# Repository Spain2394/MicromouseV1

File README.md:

# Introduction
Micromouse (small robot car) PCB, boards are  designed in [EAGLE](http://eagle.autodesk.com)

Current board release [micromouse_board_revB_V0.0.16_2020-02-19.zip ](https://github.com/uga-robotics/MicromouseV1/blob/master/micromouse-main-board/micromouse-revB/micromouse_board_revB_V0.0.16_2020-02-19.zip ). Inside this zip file you will CAM files for assembly and manufacturing. 
Board BOM  --> [micromouse_board_revB_V0.0.16_2020-02-19.xlsx](https://github.com/uga-robotics/MicromouseV1/blob/master/micromouse-main-board/micromouse-revB/micromouse_board_revB_V0.0.16.xlsx)

## Getting going
Clone to hardware of software to local machine: ```git clone --recurse-submodules https://github.com/uga-robotics/MicromouseV1.git```

# Table of contents
1. [Bill Of Materials](https://github.com/Spain2394/MicromouseV1/blob/master/Wiki/Bill-of-Materials.md)
2. [Hardware Setup](https://github.com/Spain2394/MicromouseV1/blob/master/Wiki/Hardware-Setup.md)
3. [Software Setup](https://github.com/Spain2394/MicromouseV1/blob/master/Wiki/Software-Setup.md)

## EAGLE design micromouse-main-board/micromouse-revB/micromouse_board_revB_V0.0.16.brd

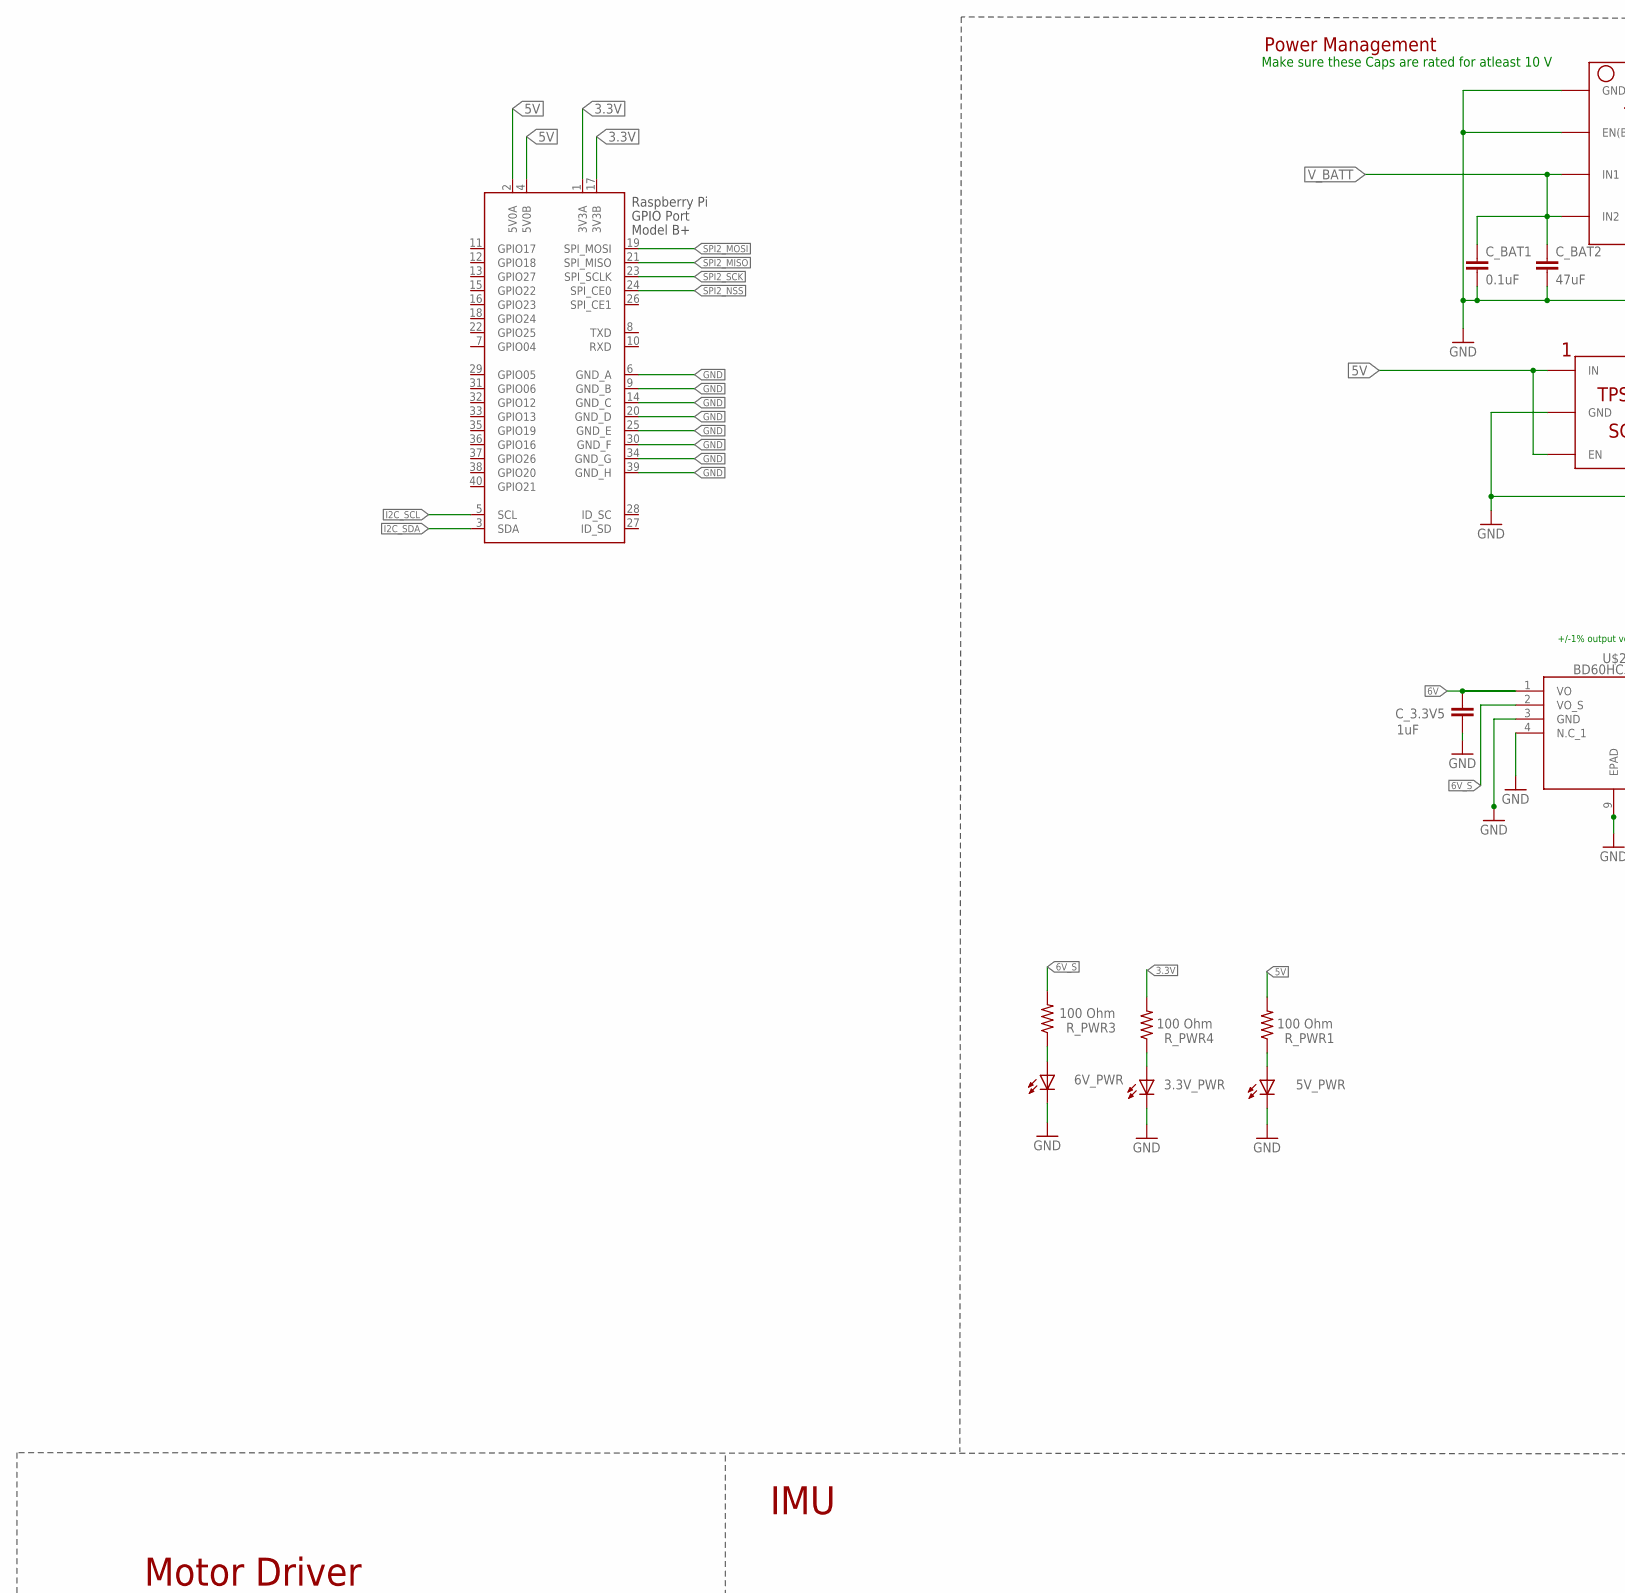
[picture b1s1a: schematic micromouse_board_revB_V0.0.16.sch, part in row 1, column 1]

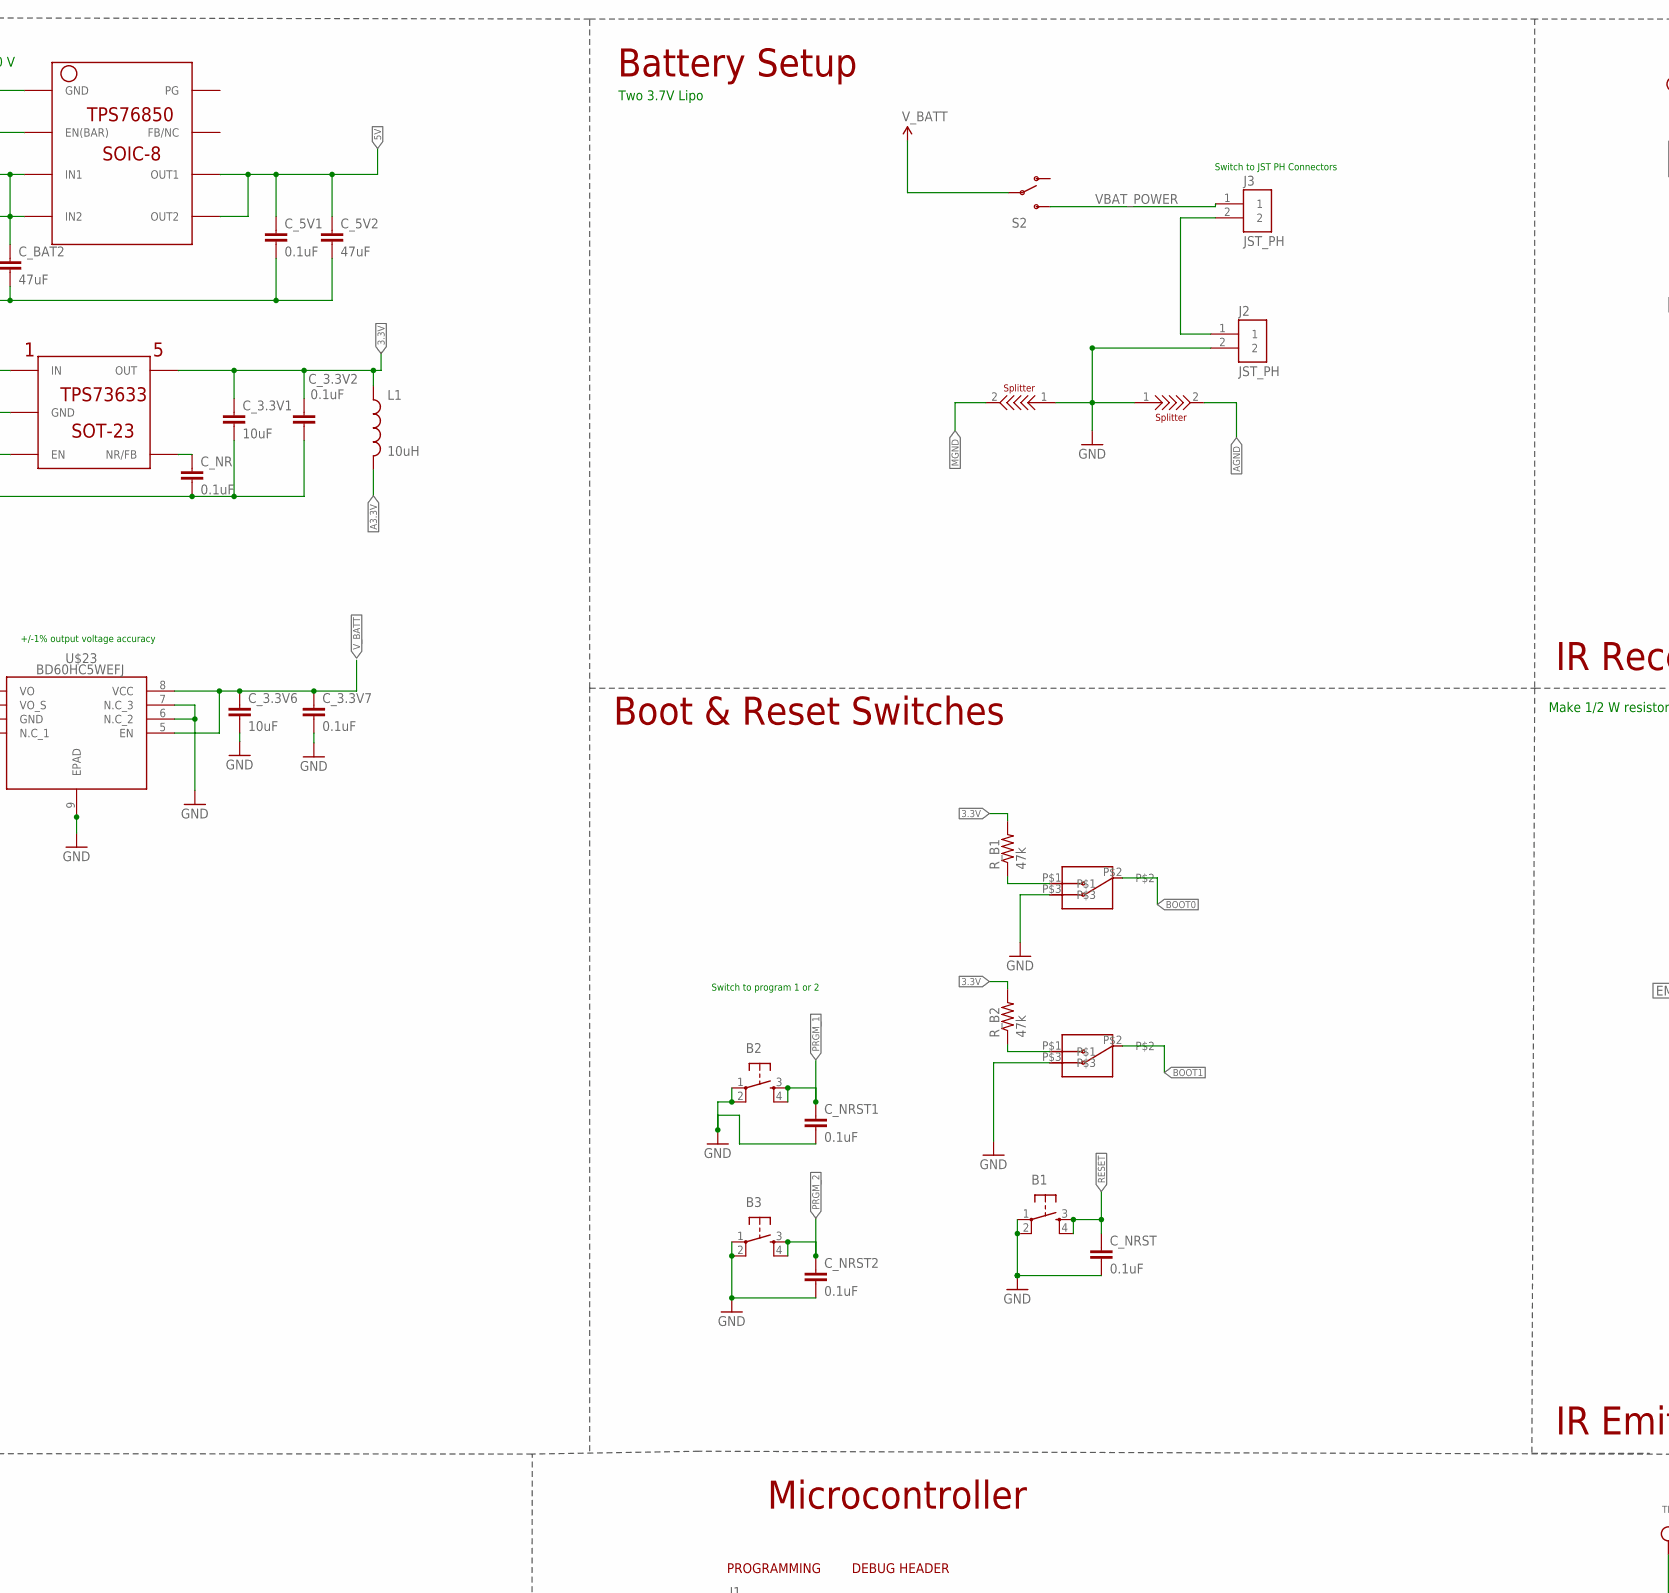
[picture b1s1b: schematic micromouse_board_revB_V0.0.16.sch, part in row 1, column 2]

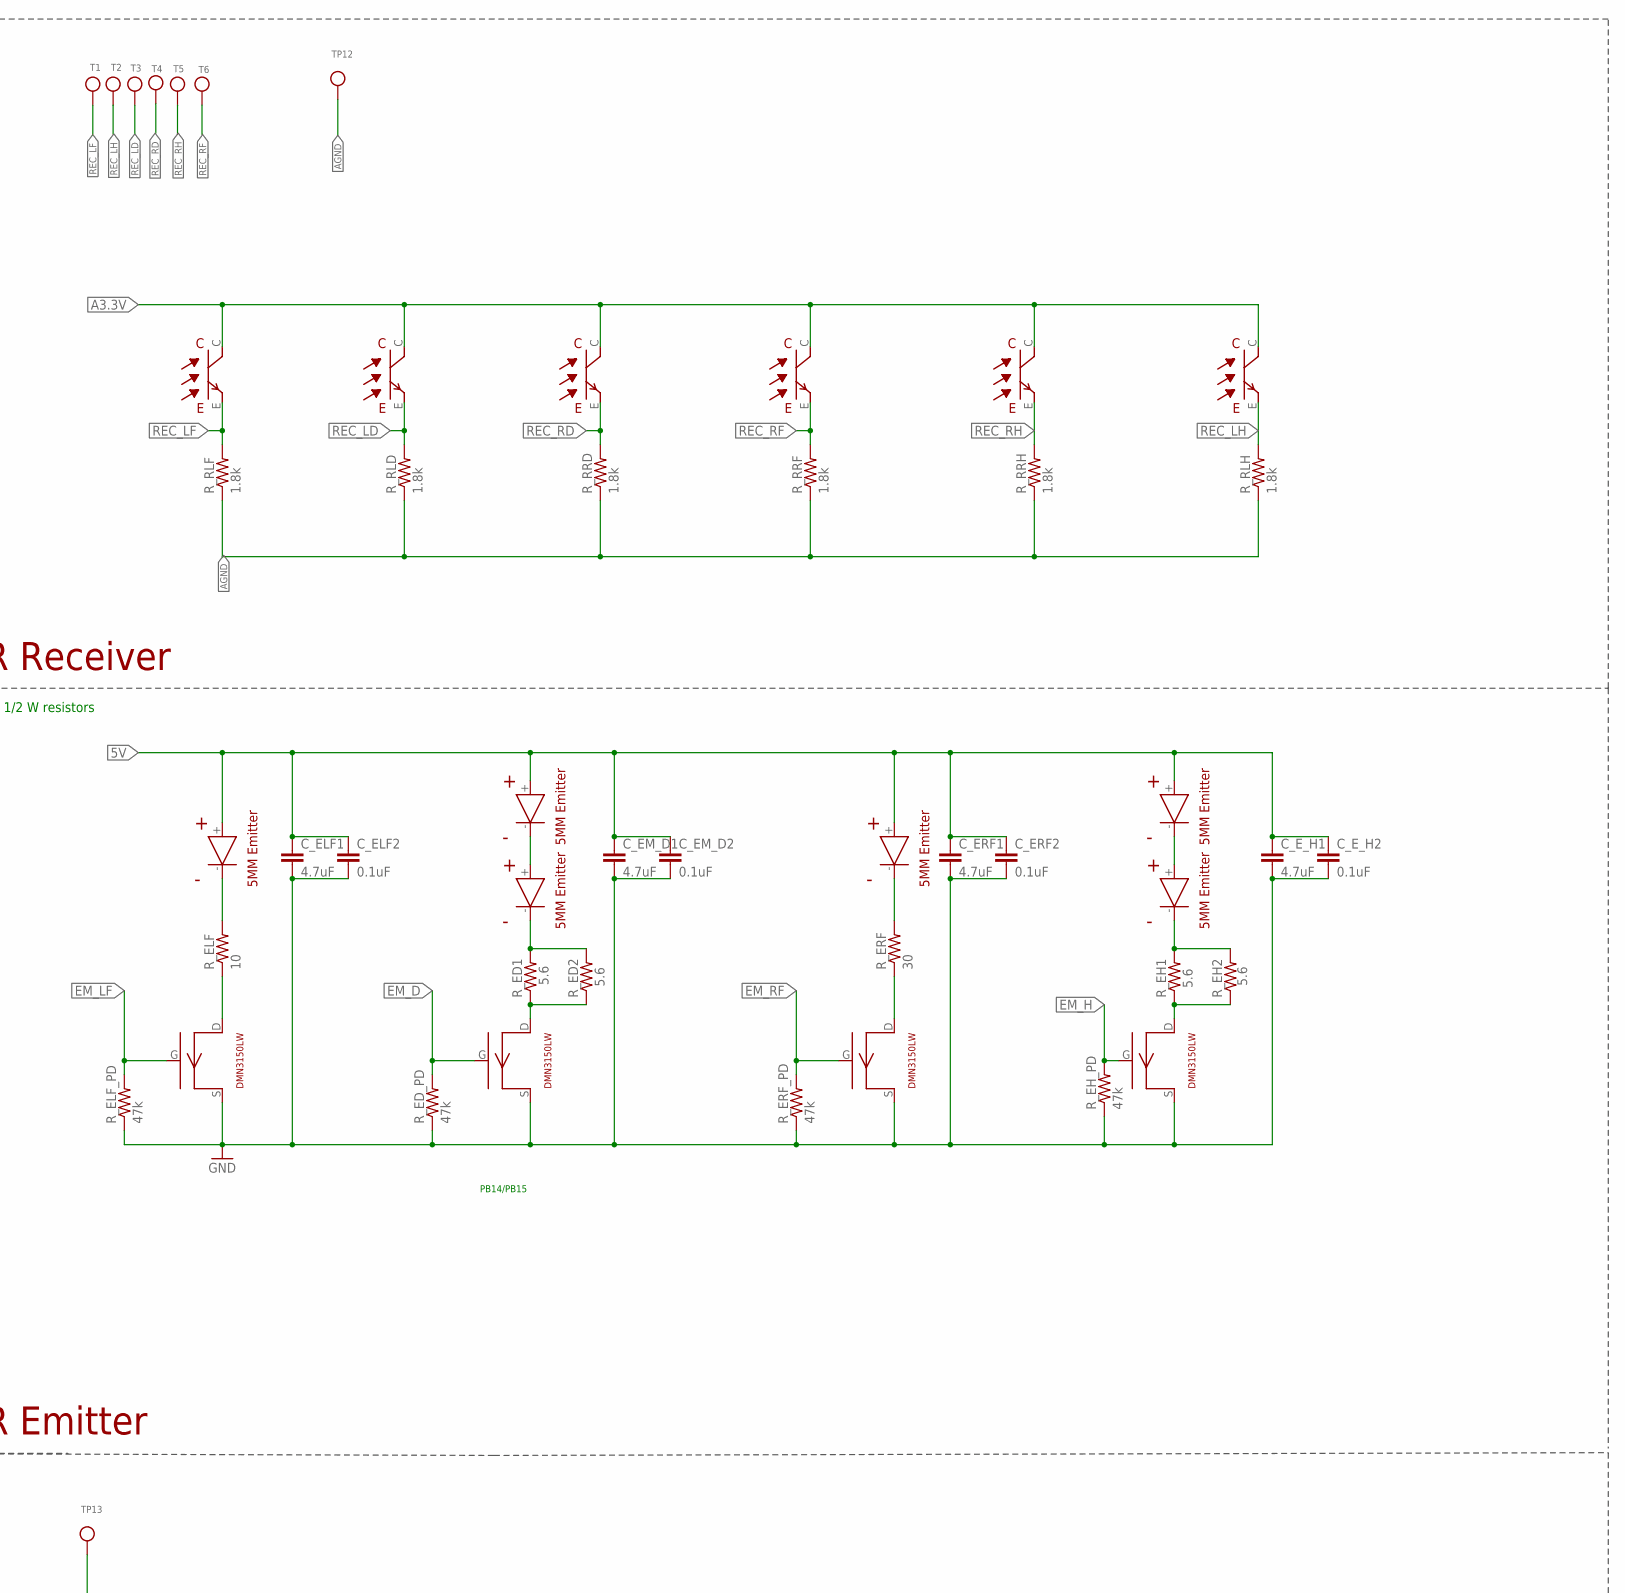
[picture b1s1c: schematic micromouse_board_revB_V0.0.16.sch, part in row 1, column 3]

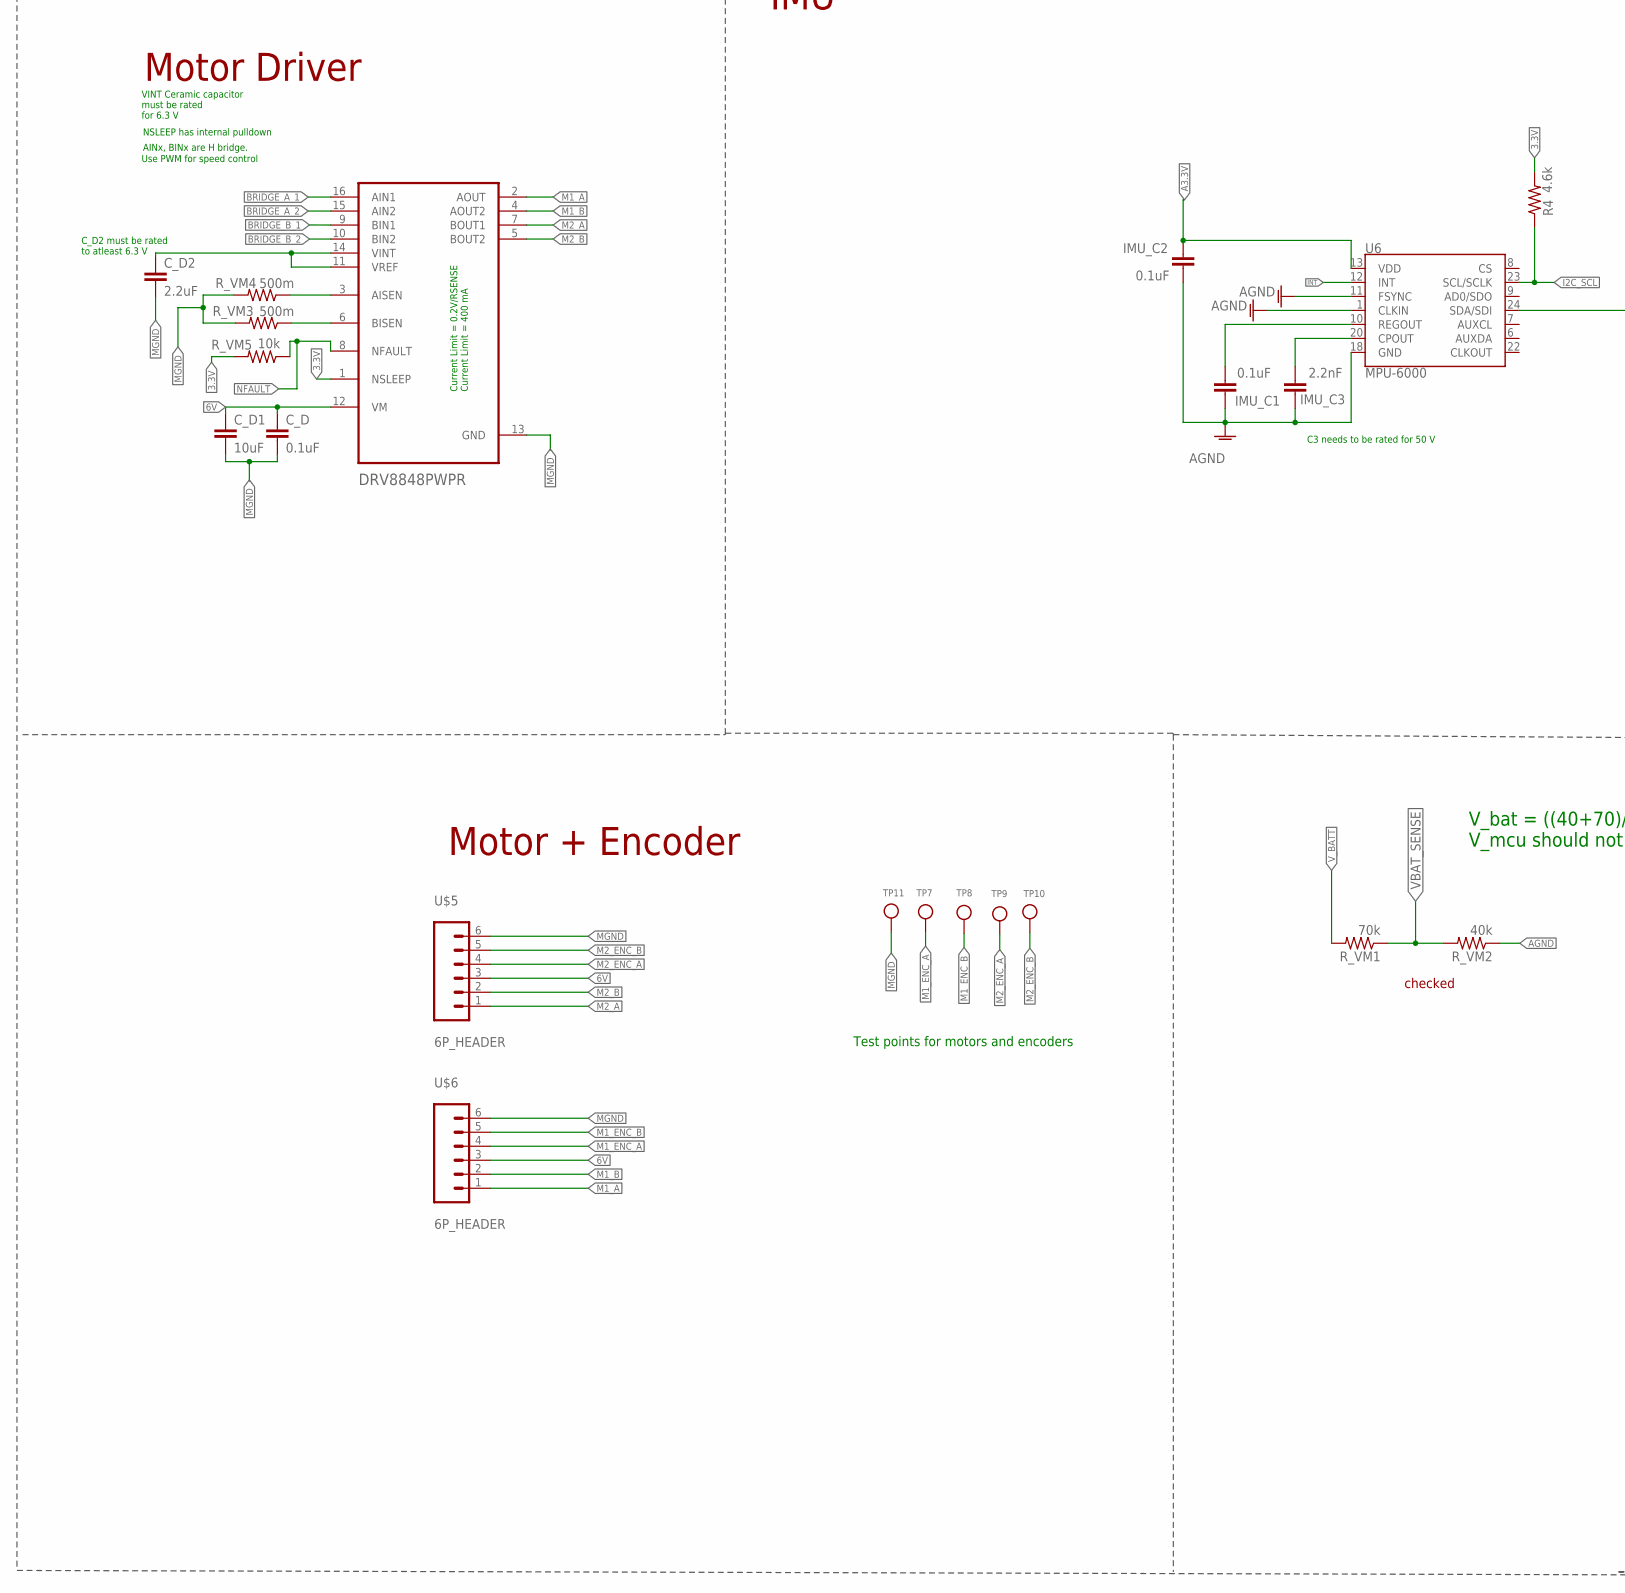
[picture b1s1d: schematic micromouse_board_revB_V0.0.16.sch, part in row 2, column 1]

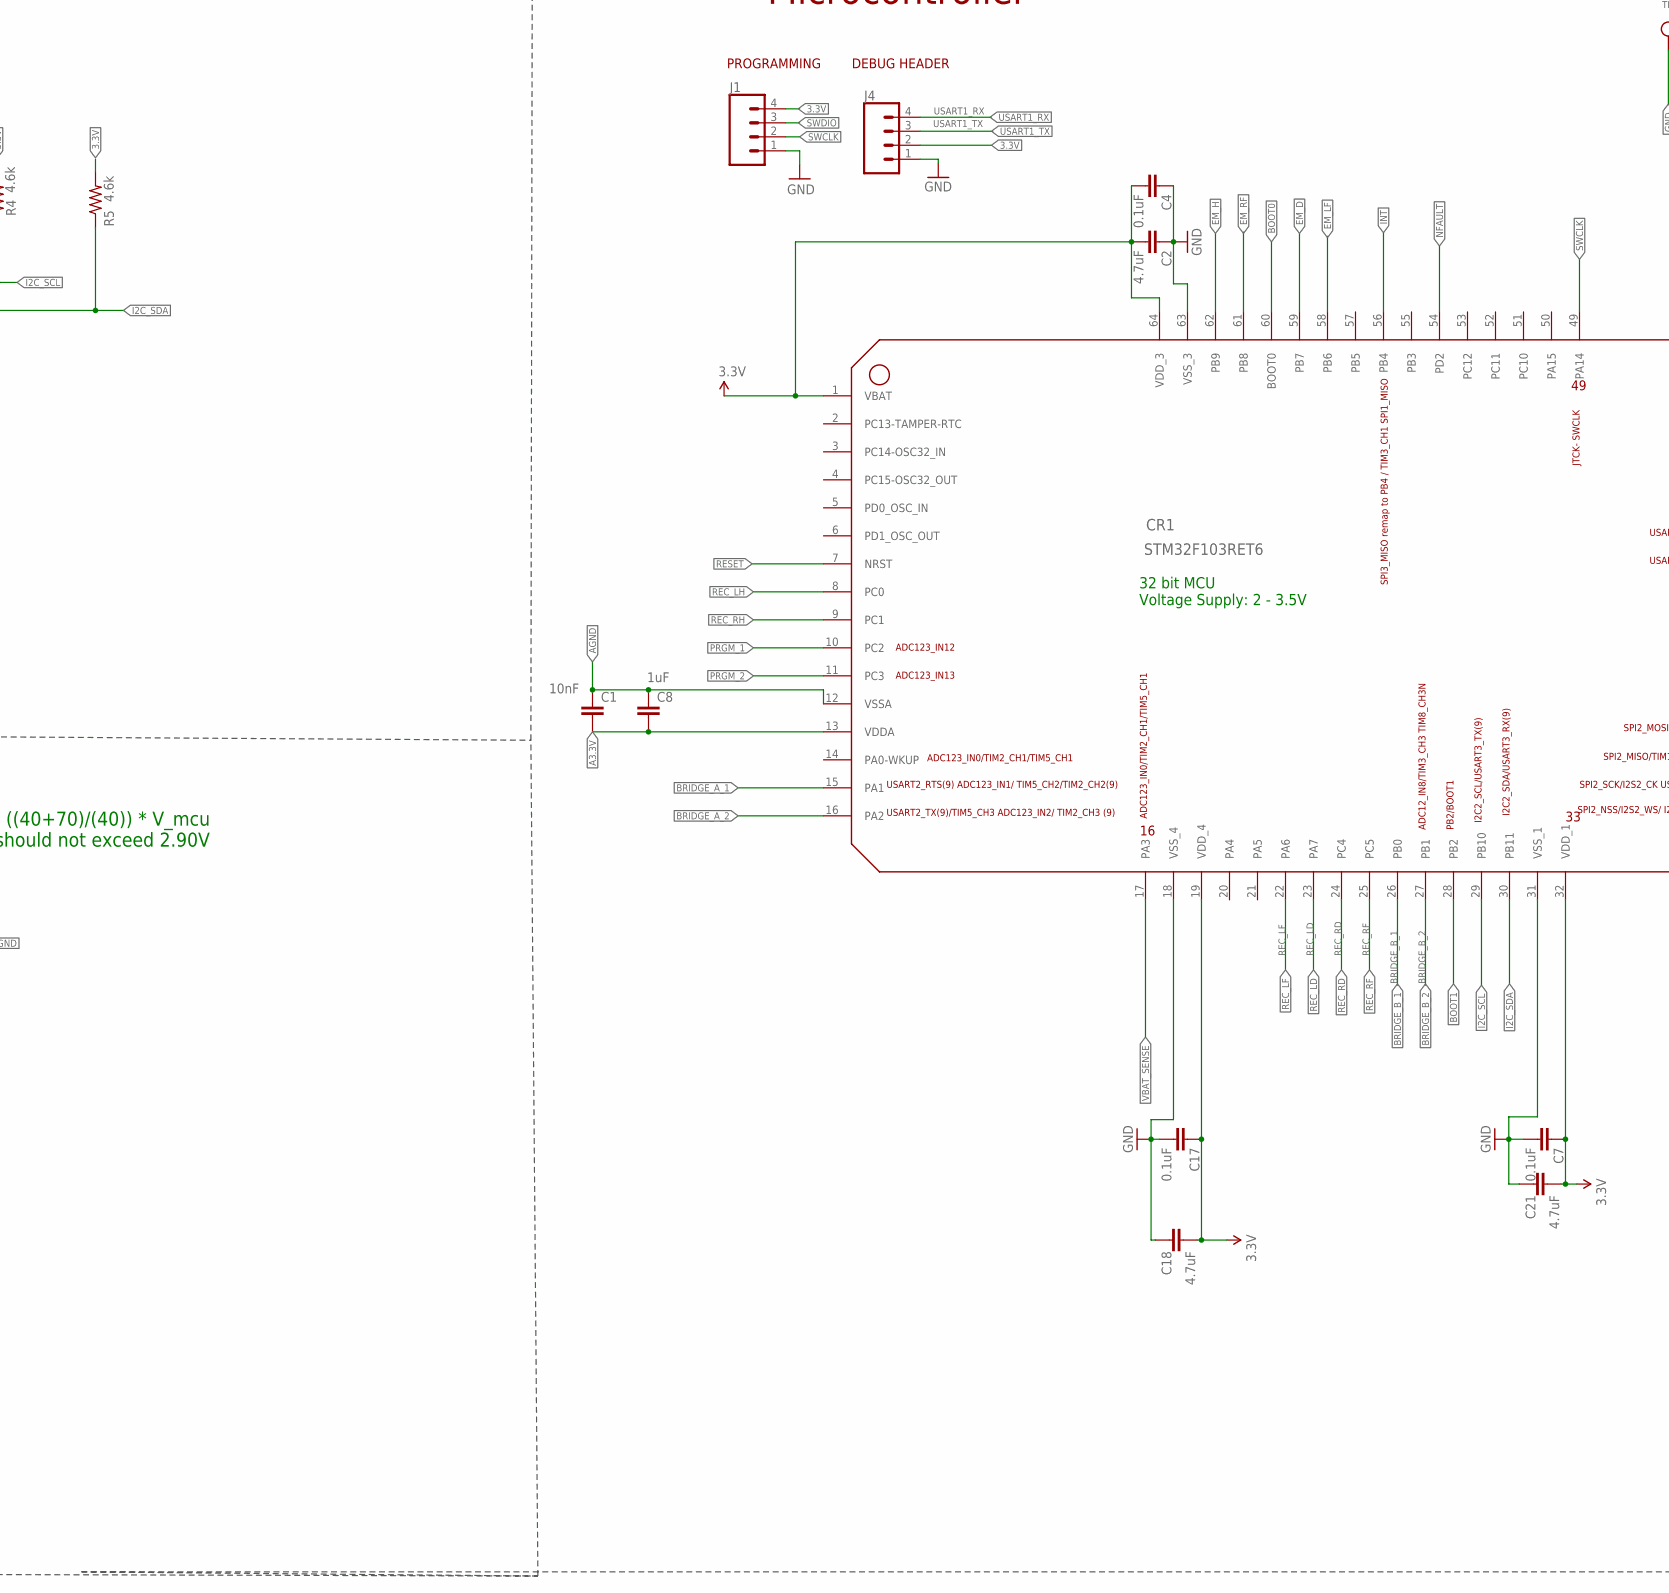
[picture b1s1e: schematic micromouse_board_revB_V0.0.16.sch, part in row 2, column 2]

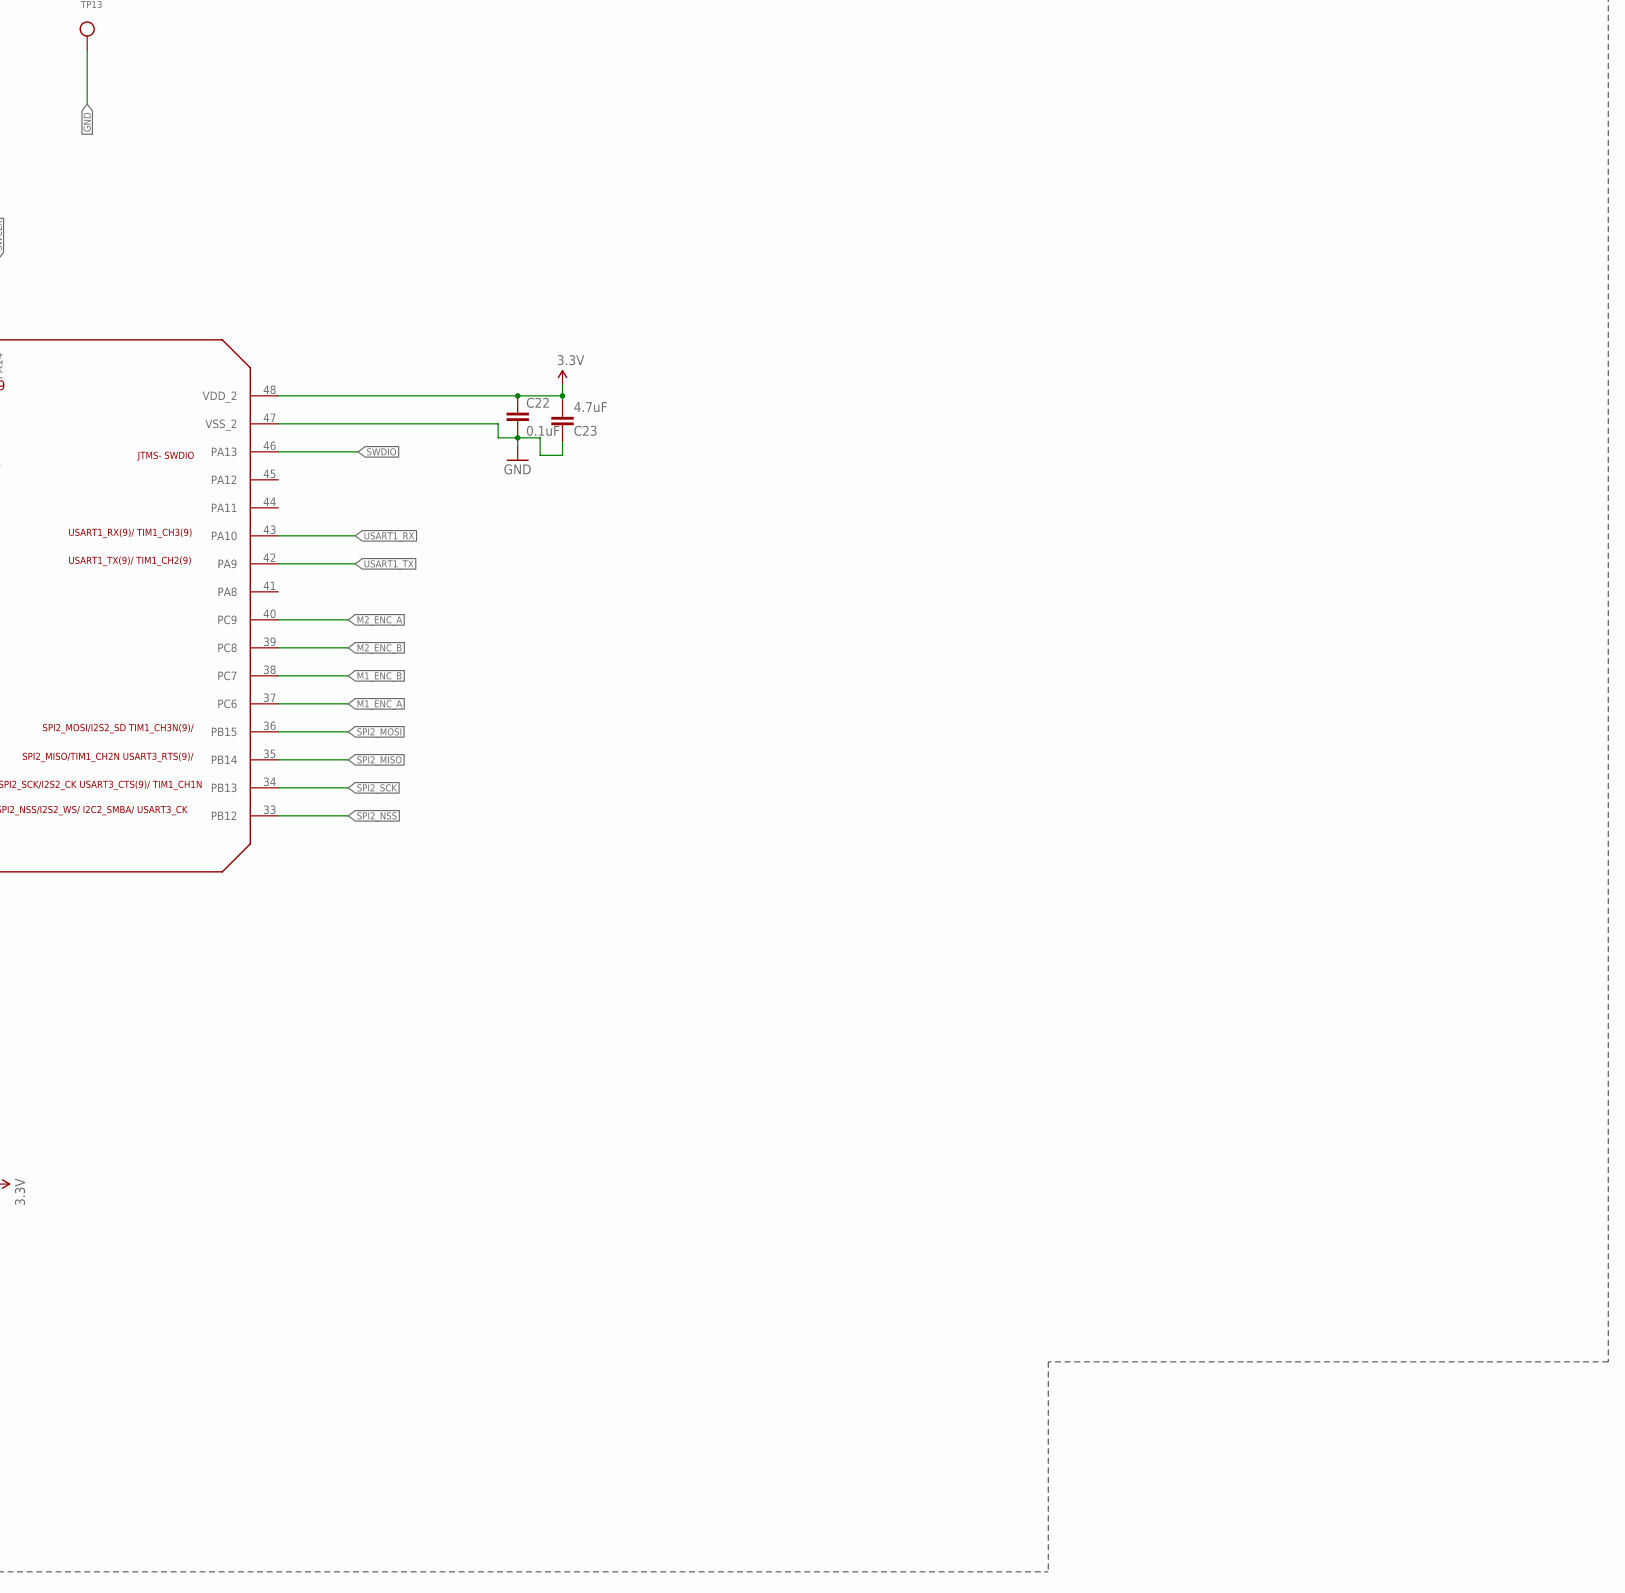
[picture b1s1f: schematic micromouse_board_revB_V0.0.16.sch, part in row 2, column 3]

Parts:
3.3V_PWR, 5V_PWR, 6V_PWR: green; LED-1206
B1, B2, B3: TAC_SWITCHSMD; TACTILE-SWITCH-SMD
C1: 10nF; 0603-CAP
C2, C18, C21, C23: 4.7uF; 0603-CAP
C4, C7, C17, C22: 0.1uF; 0603-CAP
C8: 1uF; 0603-CAP
CR1: STM32F103RET6; LQFP-64
C_3.3V1, C_3.3V6: 10uF; 0603-CAP
C_3.3V2, C_3.3V7, C_5V1: 0.1uF; 0603-CAP
C_3.3V5: 1uF; 0603-CAP
C_5V2: 47uF; 1210
C_BAT1: 0.1uF; 0603-CAP
C_BAT2: 47uF; 1210
C_D: 0.1uF; 0603-CAP
C_D1: 10uF; 0603-CAP
C_D2: 2.2uF; 0603-CAP
C_ELF1: 4.7uF; 0603-CAP
C_ELF2: 0.1uF; 0603-CAP
C_EM_D1: 4.7uF; 0603-CAP
C_EM_D2: 0.1uF; 0603-CAP
C_ERF1: 4.7uF; 0603-CAP
C_ERF2: 0.1uF; 0603-CAP
C_E_H1: 4.7uF; 0603-CAP
C_E_H2: 0.1uF; 0603-CAP
C_NR: 0.1uF; 0603-CAP
C_NRST, C_NRST1, C_NRST2: 0.1uF; 0603-CAP
IMU_C1, IMU_C2: 0.1uF; 0603-CAP
IMU_C3: 2.2nF; 0603-CAP
J1, J4: CONN_04; 1X04
J2, J3: JST_PH; JST_B2B-PH-K-S(LF)(SN)
L1: 10uH; 1007
LEFT_FRONT_EMITTER: EMITTER
NMOS1, NMOS2, NMOS3, NMOS4: DMN3150LW
R4, R5: 4.6k; M0805
REC_LF: RECEIVER
R_B1, R_B2: 47k; 0603-RES
R_ED1, R_ED2: 5.6; 0603-RES
R_ED_PD: 47k; 0603-RES
R_EH1, R_EH2: 5.6; 0603-RES
R_EH_PD: 47k; 0603-RES
R_ELF: 10; 0603-RES
R_ELF_PD: 47k; 0603-RES
R_ERF: 30; 0603-RES
R_ERF_PD: 47k; 0603-RES
R_PWR1, R_PWR3, R_PWR4: 100 Ohm; 0603-RES
R_RLD: 1.8k; 0603-RES
R_RLF: 1.8k; 0603-RES
R_RLH: 1.8k; 0603-RES
R_RRD: 1.8k; 0603-RES
R_RRF: 1.8k; 0603-RES
R_RRH: 1.8k; 0603-RES
R_VM1: 70k; 0603-RES
R_VM2: 40k; 0603-RES
R_VM3, R_VM4: 500m; 0603-RES
R_VM5: 10k; 0603-RES
S2: SWITCH-SPSTPTH; SWITCH-SPDT
T1, T2, T3, T4, T5, T6: TESTPOINTROUND2MM; TESTPOINT_ROUND_2MM
TP7, TP8, TP9, TP10, TP11, TP12, TP13: TESTPOINTROUND2MM; TESTPOINT_ROUND_2MM
U2: DRV8848PWPR; SOP65P640X120-17N
U6: MPU-6000; QFN-24-EP
U$3: TPS73633(SOT-23)
U$4: TPS76850(SOIC-8)
U$5, U$6: 6P_HEADER
U$7, U$8, U$9, U$20, U$21: RECEIVER
U$11, U$13, U$17, U$18, U$19: EMITTER
U$14, U$15: SPARKFUN-SPDT; SPDT
U$16, U$22: SPLITTER
U$23: BD60HC5WEFJ; SOIC127P600X100-9N
X1: RASPI_GPIO_B+#_PIN; RASPI_GPIO_B+_PIN

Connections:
3.3V: C2.2, C4.2, C7.1, C17.1, C18.2, C21.2, C22.1, C23.2, CR1.1 (VBAT), CR1.19 (VDD_4), CR1.32 (VDD_1), CR1.48 (VDD_2), CR1.64 (VDD_3), C_3.3V1.1, C_3.3V2.1, J1.4, J4.2, L1.1, R4.2, R5.2, R_B1.2, R_B2.2, R_PWR4.2, R_VM5.2, U2.1 (NSLEEP), U$3.OUT, X1.1 (3V3A), X1.17 (3V3B)
5V: C_5V1.1, C_5V2.1, C_ELF1.1, C_ELF2.1, C_EM_D1.1, C_EM_D2.1, C_ERF1.1, C_ERF2.1, C_E_H1.1, C_E_H2.1, LEFT_FRONT_EMITTER.+, R_PWR1.2, U$3.EN, U$3.IN, U$4.OUT1, U$4.OUT2, U$11.+, U$13.+, U$18.+, X1.2 (5V0A), X1.4 (5V0B)
6V: C_3.3V5.1, C_D.1, C_D1.1, U2.12 (VM), U$5.3, U$6.3, U$23.1 (VO)
6V_S: R_PWR3.2, U$23.2 (VO_S)
A3.3V: C1.2, C8.2, CR1.13 (VDDA), IMU_C2.1, L1.2, REC_LF.C, U6.13 (VDD), U$7.C, U$8.C, U$9.C, U$20.C, U$21.C
AGND: C1.1, C8.1, CR1.12 (VSSA), IMU_C1.2, IMU_C2.2, IMU_C3.2, R_RLD.1, R_RLF.1, R_RLH.1, R_RRD.1, R_RRF.1, R_RRH.1, R_VM2.1, TP12.P$1, U6.1 (CLKIN), U6.11 (FSYNC), U6.18 (GND), U$22.2
BOOT0: CR1.60 (BOOT0), U$14.P$2
BOOT1: CR1.28 (PB2), U$15.P$2
BRIDGE_A_1: CR1.15 (PA1), U2.16 (AIN1)
BRIDGE_A_2: CR1.16 (PA2), U2.15 (AIN2)
BRIDGE_B_1: CR1.26 (PB0), U2.9 (BIN1)
BRIDGE_B_2: CR1.27 (PB1), U2.10 (BIN2)
D2_EM: R_ED1.2, R_ED2.2, U$17.-
D_EM: U$11.-, U$17.+
EM_D: CR1.59 (PB7), NMOS2.G, R_ED_PD.2
EM_H: CR1.62 (PB9), NMOS4.G, R_EH_PD.2
EM_LF: CR1.58 (PB6), NMOS1.G, R_ELF_PD.2
EM_RF: CR1.61 (PB8), NMOS3.G, R_ERF_PD.2
GND: 3.3V_PWR.C, 5V_PWR.C, 6V_PWR.C, B1.1, B1.2, B2.1, B2.2, B3.1, B3.2, C2.1, C4.1, C7.2, C17.2, C18.1, C21.1, C22.2, C23.1, CR1.18 (VSS_4), CR1.31 (VSS_1), CR1.47 (VSS_2), CR1.63 (VSS_3), C_3.3V1.2, C_3.3V2.2, C_3.3V5.2, C_3.3V6.2, C_3.3V7.2, C_5V1.2, C_5V2.2, C_BAT1.2, C_BAT2.2, C_ELF1.2, C_ELF2.2, C_EM_D1.2, C_EM_D2.2, C_ERF1.2, C_ERF2.2, C_E_H1.2, C_E_H2.2, C_NR.2, C_NRST.2, C_NRST1.2, C_NRST2.2, J1.1, J2.2, J4.1, NMOS1.S, NMOS2.S, NMOS3.S, NMOS4.S, R_ED_PD.1, R_EH_PD.1, R_ELF_PD.1, R_ERF_PD.1, TP13.P$1, U$3.GND, U$4.EN(BAR), U$4.GND, U$14.P$3, U$15.P$3, U$16.1, U$22.1, U$23.3 (GND), U$23.4 (N.C_1), U$23.6 (N.C_2), U$23.7 (N.C_3), U$23.9 (EPAD), X1.6 (GND_A), X1.9 (GND_B), X1.14 (GND_C), X1.20 (GND_D), X1.25 (GND_E), X1.30 (GND_F), X1.34 (GND_G), X1.39 (GND_H)
H2_EM: R_EH1.2, R_EH2.2, U$19.-
H_EM: U$18.-, U$19.+
I2C_SCL: CR1.29 (PB10), R4.1, U6.23 (SCL/SCLK), X1.5 (SCL)
I2C_SDA: CR1.30 (PB11), R5.1, U6.24 (SDA/SDI), X1.3 (SDA)
INT: CR1.56 (PB4), U6.12 (INT)
LF_EM: LEFT_FRONT_EMITTER.-, R_ELF.2
M1_A: U2.2 (AOUT), U$6.1
M1_B: U2.4 (AOUT2), U$6.2
M1_ENC_A: CR1.37 (PC6), TP7.P$1, U$6.4
M1_ENC_B: CR1.38 (PC7), TP8.P$1, U$6.5
M2_A: U2.7 (BOUT1), U$5.1
M2_B: U2.5 (BOUT2), U$5.2
M2_ENC_A: CR1.40 (PC9), TP9.P$1, U$5.4
M2_ENC_B: CR1.39 (PC8), TP10.P$1, U$5.5
MGND: C_D.2, C_D1.2, C_D2.2, R_VM3.2, R_VM4.2, TP11.P$1, U2.13 (GND), U$5.6 (8), U$6.6 (8), U$16.2
unnamed: 3.3V_PWR.A, R_PWR4.1
unnamed: R_VM4.1, U2.3 (AISEN)
unnamed: J2.1, J3.2
unnamed: R_B2.1, U$15.P$1
unnamed: NMOS3.D, R_ERF.1
unnamed: R_B1.1, U$14.P$1
unnamed: NMOS1.D, R_ELF.1
unnamed: R_VM3.1, U2.6 (BISEN)
unnamed: 6V_PWR.A, R_PWR3.1
unnamed: C_D2.1, U2.11 (VREF), U2.14 (VINT)
unnamed: 5V_PWR.A, R_PWR1.1
unnamed: NMOS2.D, R_ED1.1, R_ED2.1
unnamed: NMOS4.D, R_EH1.1, R_EH2.1
unnamed: C_NR.1, U$3.NR/FB
unnamed: IMU_C1.1, U6.10 (REGOUT)
unnamed: IMU_C3.1, U6.20 (CPOUT)
NFAULT: CR1.54 (PD2), R_VM5.1, U2.8 (NFAULT)
PRGM_1: B2.3, B2.4, CR1.10 (PC2), C_NRST1.1
PRGM_2: B3.3, B3.4, CR1.11 (PC3), C_NRST2.1
REC_LD: CR1.23 (PA7), R_RLD.2, T3.P$1, U$7.E
REC_LF: CR1.22 (PA6), REC_LF.E, R_RLF.2, T1.P$1
REC_LH: CR1.8 (PC0), R_RLH.2, T2.P$1, U$21.E
REC_RD: CR1.24 (PC4), R_RRD.2, T4.P$1, U$8.E
REC_RF: CR1.25 (PC5), R_RRF.2, T6.P$1, U$9.E
REC_RH: CR1.9 (PC1), R_RRH.2, T5.P$1, U$20.E
RESET: B1.3, B1.4, CR1.7 (NRST), C_NRST.1
RF_EM: R_ERF.2, U$13.-
SPI2_MISO: CR1.35 (PB14), X1.21 (SPI_MISO)
SPI2_MOSI: CR1.36 (PB15), X1.19 (SPI_MOSI)
SPI2_NSS: CR1.33 (PB12), X1.24 (SPI_CE0)
SPI2_SCK: CR1.34 (PB13), X1.23 (SPI_SCLK)
SWCLK: CR1.49 (PA14), J1.2
SWDIO: CR1.46 (PA13), J1.3
USART1_RX: CR1.43 (PA10), J4.4
USART1_TX: CR1.42 (PA9), J4.3
VBAT_POWER: J3.1, S2.3 (S)
VBAT_SENSE: CR1.17 (PA3), R_VM1.1, R_VM2.2
V_BATT: C_3.3V6.1, C_3.3V7.1, C_BAT1.1, C_BAT2.1, R_VM1.2, S2.2, U$4.IN1, U$4.IN2, U$23.5 (EN), U$23.8 (VCC)

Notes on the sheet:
32 bit MCU Voltage Supply: 2 - 3.5V
PROGRAMMING DEBUG HEADER
Microcontroller
Motor + Encoder
Motor Driver
IR Emitter
IR Receiver
IMU
V_bat = ((40+70)/(40)) * V_mcu V_mcu should not exceed 2.90V
Battery Setup
ADC123_IN0/TIM2_CH1/TIM5_CH1
VINT Ceramic capacitor must be rated for 6.3 V
NSLEEP has internal pulldown
Current Limit = 0.2V/RSENSE Current Limit = 400 mA
AINx, BINx are H bridge.
Use PWM for speed control
PB14/PB15
checked
Power Management
Test points for motors and encoders
C_D2 must be rated to atleast 6.3 V
ADC12_IN8/TIM3_CH3 TIM8_CH3N
USART2_RTS(9) ADC123_IN1/ TIM5_CH2/TIM2_CH2(9)
USART2_TX(9)/TIM5_CH3 ADC123_IN2/ TIM2_CH3 (9)
I2C2_SCL/USART3_TX(9)
I2C2_SDA/USART3_RX(9)
SPI2_NSS/I2S2_WS/ I2C2_SMBA/ USART3_CK
SPI2_SCK/I2S2_CK USART3_CTS(9)/ TIM1_CH1N
SPI2_MISO/TIM1_CH2N USART3_RTS(9)/
SPI2_MOSI/I2S2_SD TIM1_CH3N(9)/
USART1_RX(9)/ TIM1_CH3(9)
USART1_TX(9)/ TIM1_CH2(9)
JTMS- SWDIO
JTCK- SWCLK
PB2/BOOT1
Boot & Reset Switches
Two 3.7V Lipo
Switch to JST PH Connectors
+/-1% output voltage accuracy
C3 needs to be rated for 50 V

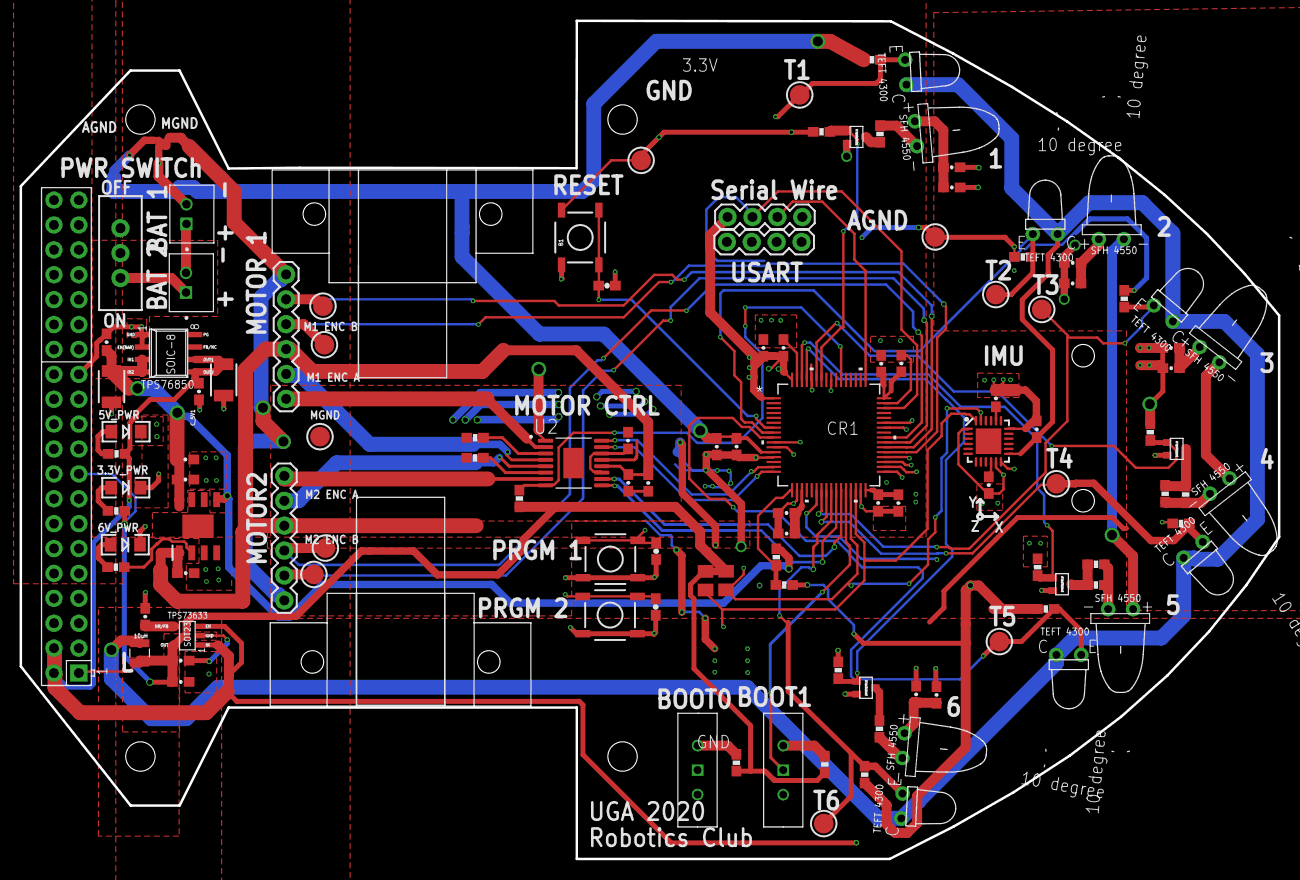
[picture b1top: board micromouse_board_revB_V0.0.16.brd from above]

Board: 4 copper layers, 128.4 x 85.5 mm, 119 parts (0 on the bottom side), 72 nets.

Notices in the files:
parts and their libraries:
SparkFun-Electromechanical: Licensing: Creative Commons ShareAlike 4.0 International - https://creativecommons.org/licenses/by-sa/4.0
SparkFun: Licensing: CC v3.0 Share-Alike You are welcome to use this library for commercial purposes.
